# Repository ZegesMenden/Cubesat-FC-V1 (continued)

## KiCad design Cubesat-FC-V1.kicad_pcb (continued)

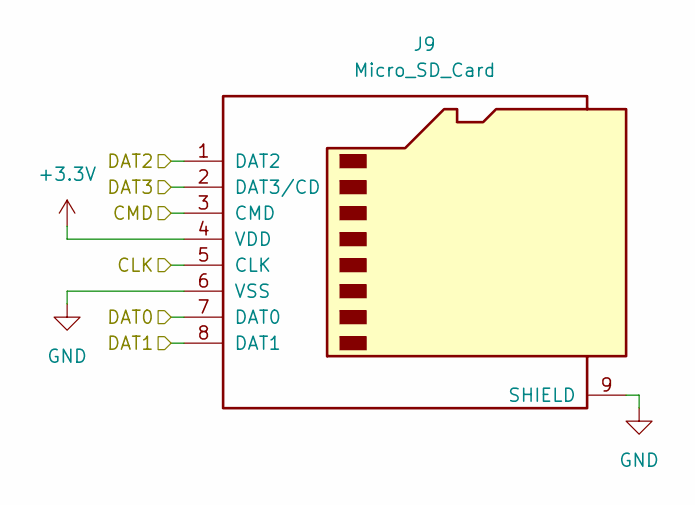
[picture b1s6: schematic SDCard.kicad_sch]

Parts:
J9: Micro_SD_Card; microSD_HC_Hirose_DM3D-SF

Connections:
+3.3V: J9.4 (VDD); also elsewhere on the board
/SD Card/CLK: J9.5 (CLK); also elsewhere on the board
/SD Card/CMD: J9.3 (CMD); also elsewhere on the board
/SD Card/DAT0: J9.7 (DAT0); also elsewhere on the board
/SD Card/DAT1: J9.8 (DAT1); also elsewhere on the board
/SD Card/DAT2: J9.1 (DAT2); also elsewhere on the board
/SD Card/DAT3: J9.2 (DAT3/CD); also elsewhere on the board
GND: J9.6 (VSS), J9.9 (SHIELD); also elsewhere on the board

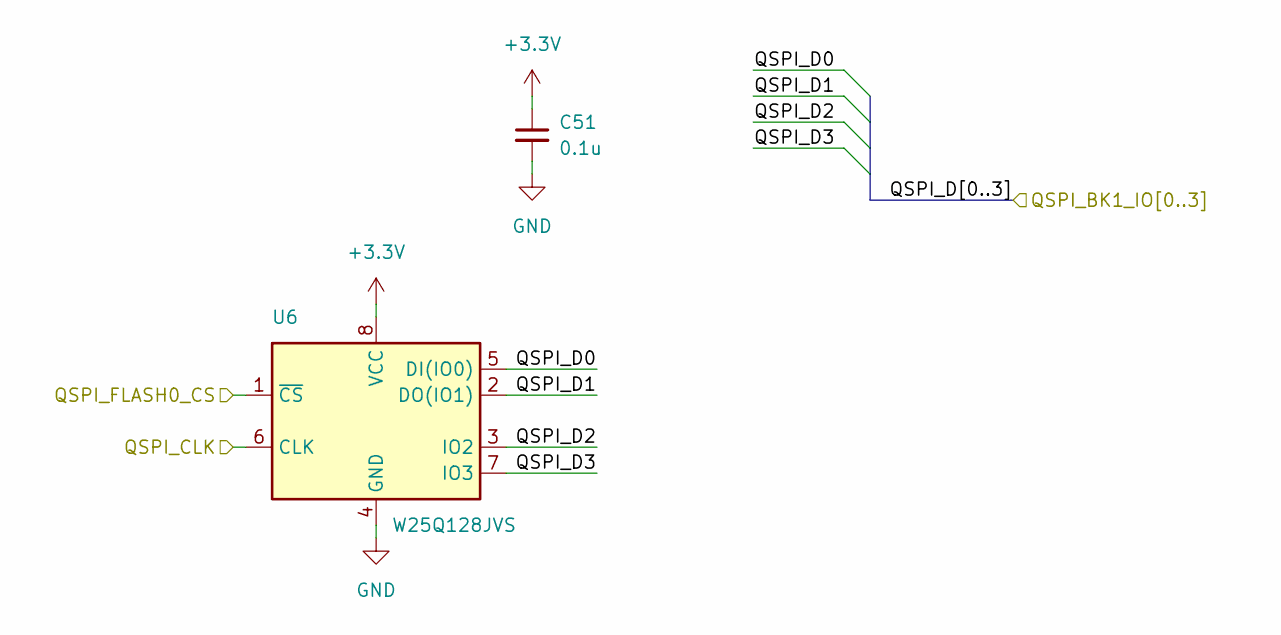
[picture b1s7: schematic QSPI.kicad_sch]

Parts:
C51: 0.1u; C_0402_1005Metric; voltage 10
U6: W25Q128JVS; SOIC-8_5.3x5.3mm_P1.27mm

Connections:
+3.3V: C51.1, U6.8 (VCC); also elsewhere on the board
/QSPI Flash/QSPI_D0: U6.5 (DI(IO0)); also elsewhere on the board
/QSPI Flash/QSPI_D1: U6.2 (DO(IO1)); also elsewhere on the board
/QSPI Flash/QSPI_D2: U6.3 (IO2); also elsewhere on the board
/QSPI Flash/QSPI_D3: U6.7 (IO3); also elsewhere on the board
/QSPI Flash/QSPI_FLASH0_CS: U6.1 (~CS); also elsewhere on the board
/STM32H747/QSPI_CLK: U6.6 (CLK); also elsewhere on the board
GND: C51.2, U6.4 (GND); also elsewhere on the board

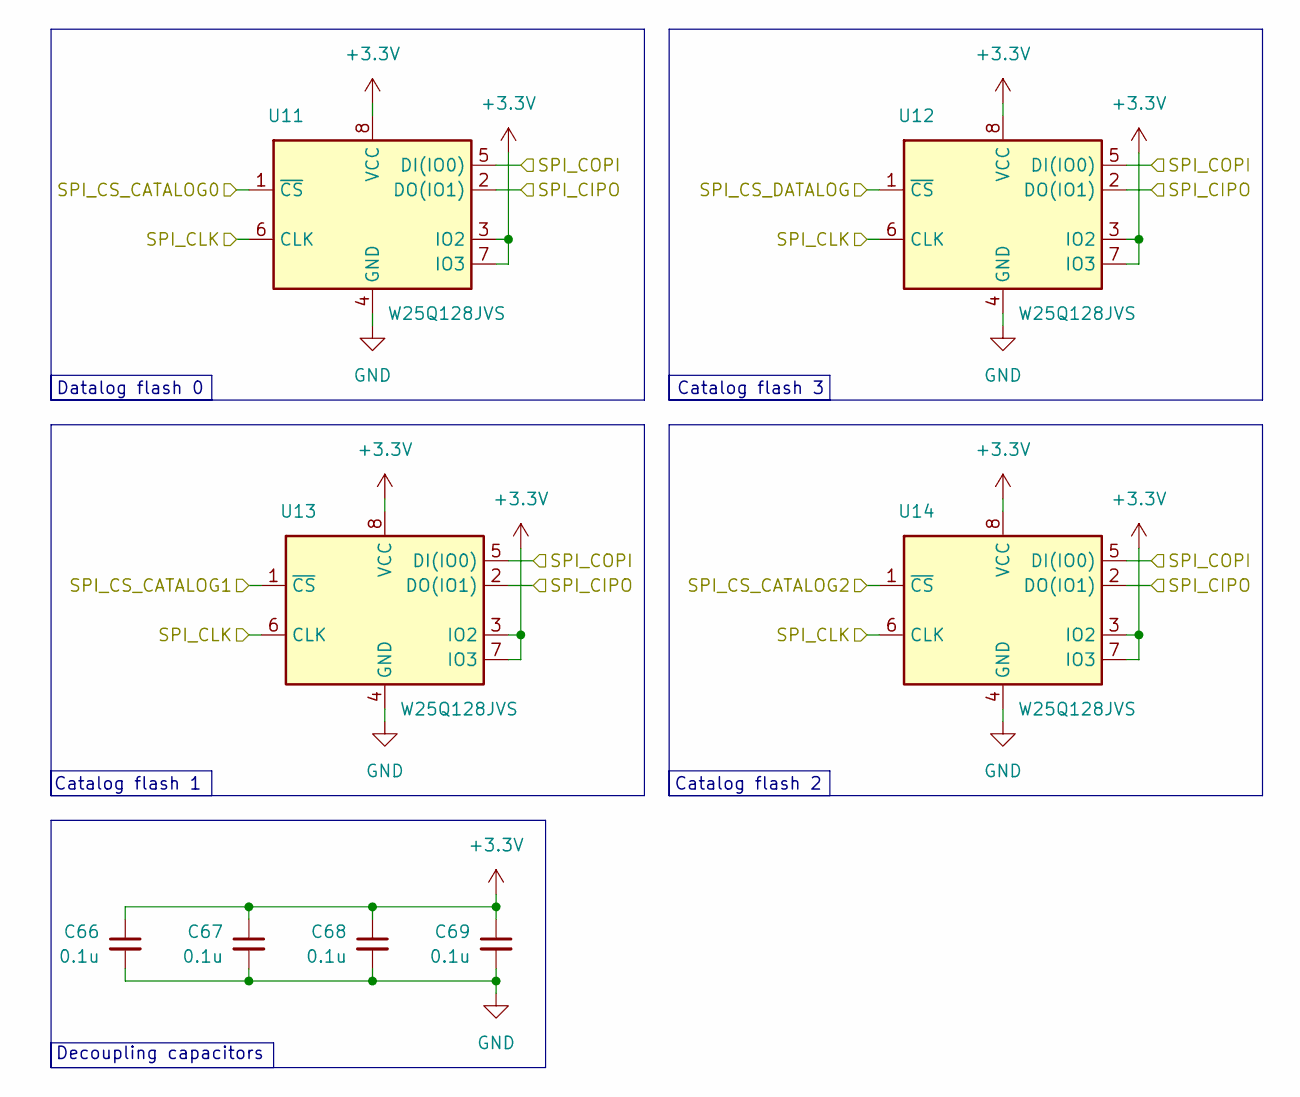
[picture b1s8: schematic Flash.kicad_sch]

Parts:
C66, C67, C68, C69: 0.1u; C_0402_1005Metric; voltage 10
U11, U12, U13, U14: W25Q128JVS; SOIC-8_5.3x5.3mm_P1.27mm

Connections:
+3.3V: C66.1, C67.1, C68.1, C69.1, U11.3 (IO2), U11.7 (IO3), U11.8 (VCC), U12.3 (IO2), U12.7 (IO3), U12.8 (VCC), U13.3 (IO2), U13.7 (IO3), U13.8 (VCC), U14.3 (IO2), U14.7 (IO3), U14.8 (VCC); also elsewhere on the board
/SPI1_CIPO: U11.2 (DO(IO1)), U12.2 (DO(IO1)), U13.2 (DO(IO1)), U14.2 (DO(IO1)); also elsewhere on the board
/SPI1_COPI: U11.5 (DI(IO0)), U12.5 (DI(IO0)), U13.5 (DI(IO0)), U14.5 (DI(IO0)); also elsewhere on the board
/SPI1_SCK: U11.6 (CLK), U12.6 (CLK), U13.6 (CLK), U14.6 (CLK); also elsewhere on the board
/SPI_CS_CATALOG0: U11.1 (~CS); also elsewhere on the board
/SPI_CS_CATALOG1: U13.1 (~CS); also elsewhere on the board
/SPI_CS_CATALOG2: U14.1 (~CS); also elsewhere on the board
/SPI_CS_DATALOG: U12.1 (~CS); also elsewhere on the board
GND: C66.2, C67.2, C68.2, C69.2, U11.4 (GND), U12.4 (GND), U13.4 (GND), U14.4 (GND); also elsewhere on the board

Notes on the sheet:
Decoupling capacitors
Catalog flash 1
Catalog flash 2
Datalog flash 0
Catalog flash 3

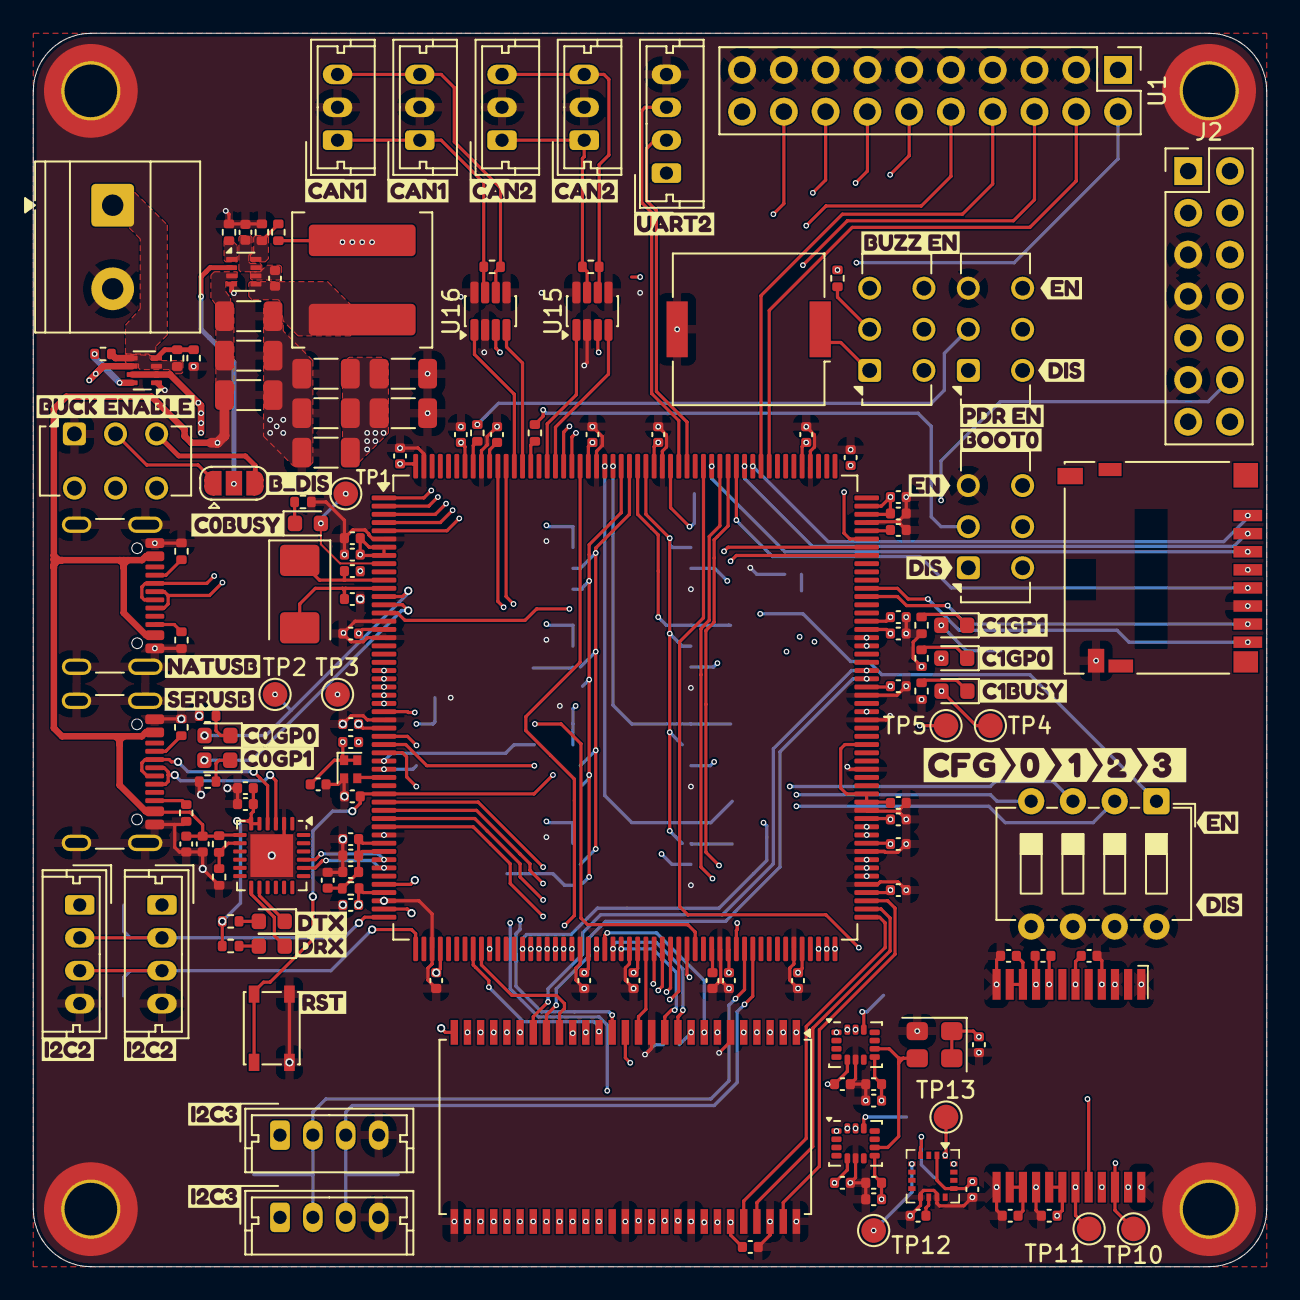
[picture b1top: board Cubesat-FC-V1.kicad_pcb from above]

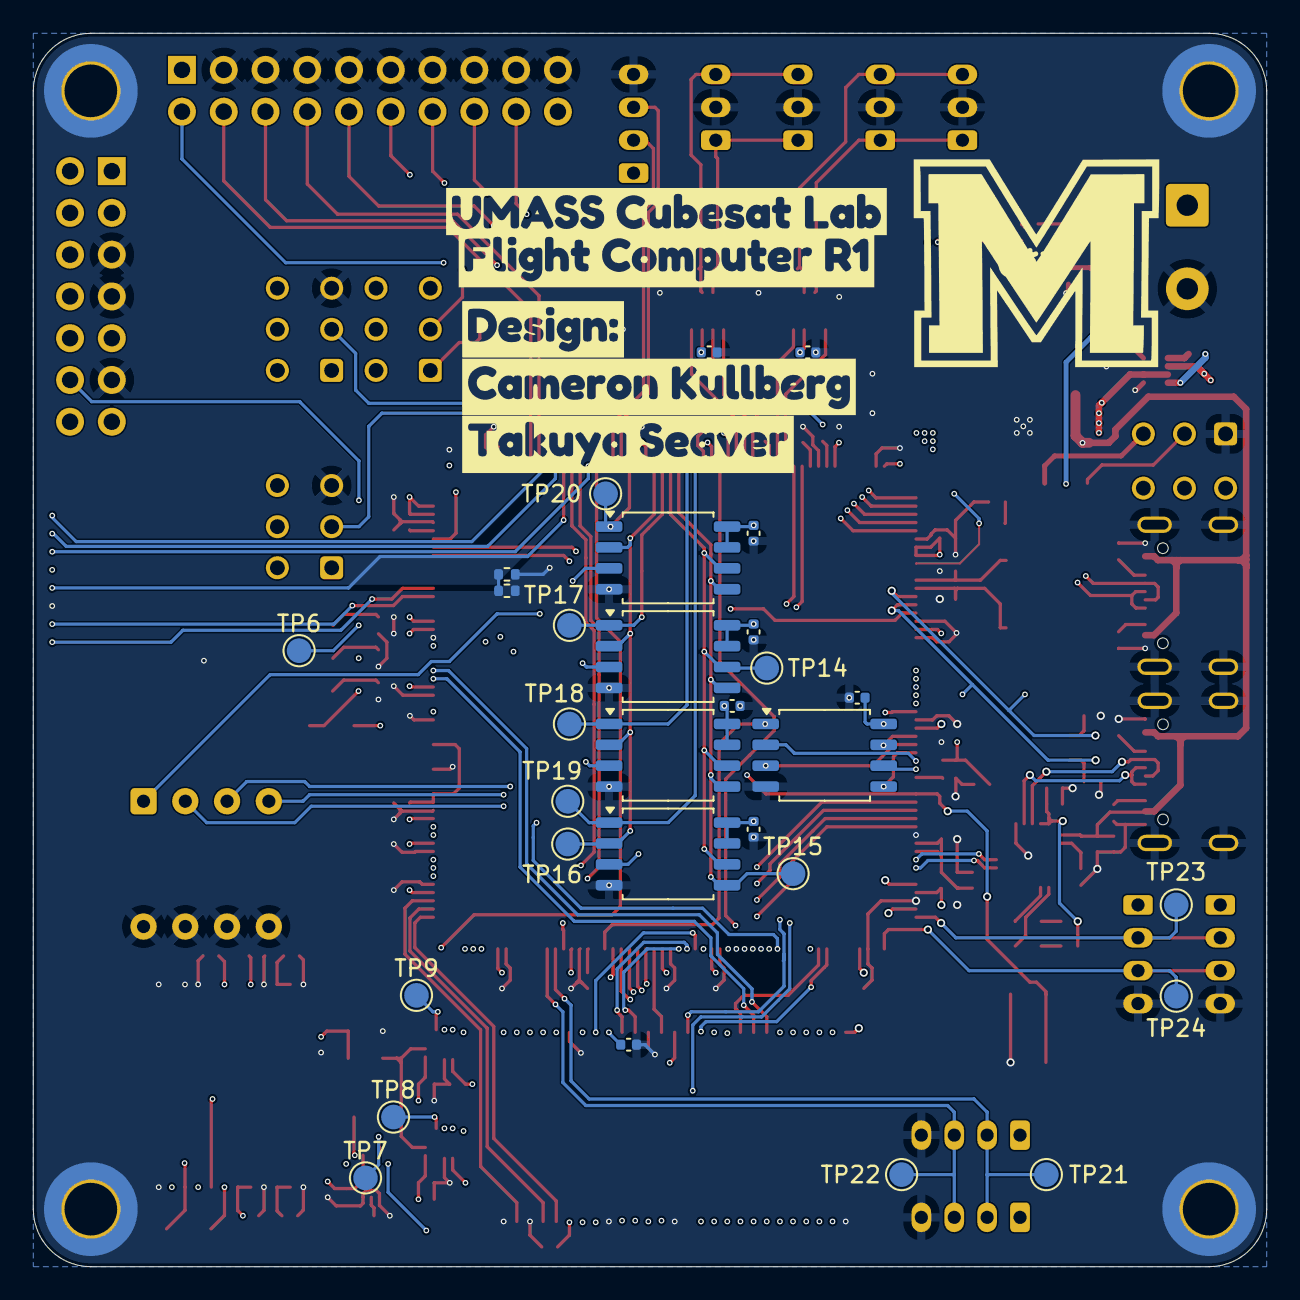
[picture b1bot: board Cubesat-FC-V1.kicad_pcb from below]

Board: 4 copper layers, 75.0 x 75.0 mm, 222 parts (35 on the bottom side), 157 nets.

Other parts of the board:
kibuzzard-69B9AFC9: G***; kibuzzard-69B9AFC9
kibuzzard-69B9BE8E: G***; kibuzzard-69B9BE8E
kibuzzard-69B9BE9C: G***; kibuzzard-69B9BE9C
kibuzzard-69B9BE81: G***; kibuzzard-69B9BE81
kibuzzard-69B64A9E: G***; kibuzzard-69B64A9E
kibuzzard-69B64AB5: G***; kibuzzard-69B64AB5
kibuzzard-69B64C2A, kibuzzard-69B64C2A#2: G***; kibuzzard-69B64C2A
kibuzzard-69B64C5E: G***; kibuzzard-69B64C5E
kibuzzard-69B64C7E, kibuzzard-69B64C7E#2: G***; kibuzzard-69B64C7E
kibuzzard-69B64C8D, kibuzzard-69B64C8D#2: G***; kibuzzard-69B64C8D
kibuzzard-69B64C48, kibuzzard-69B64C48#2: G***; kibuzzard-69B64C48
kibuzzard-69B64D23: G***; kibuzzard-69B64D23
kibuzzard-69B64D30: G***; kibuzzard-69B64D30
kibuzzard-69B64D62: G***; kibuzzard-69B64D62
kibuzzard-69B74E8C: G***; kibuzzard-69B74E8C
kibuzzard-69B753B2: G***; kibuzzard-69B753B2
kibuzzard-69B753C8: G***; kibuzzard-69B753C8
kibuzzard-69B755D8: G***; kibuzzard-69B755D8
kibuzzard-69B755DD: G***; kibuzzard-69B755DD
kibuzzard-69B7542C, kibuzzard-69B7542C#2: G***; kibuzzard-69B7542C
kibuzzard-69B7545E: G***; kibuzzard-69B7545E
kibuzzard-69B7546B: G***; kibuzzard-69B7546B
kibuzzard-69B75433, kibuzzard-69B75433#2: G***; kibuzzard-69B75433
kibuzzard-69B75457: G***; kibuzzard-69B75457
kibuzzard-69B75463: G***; kibuzzard-69B75463
kibuzzard-69B75470: G***; kibuzzard-69B75470
kibuzzard-69BF6ED0: G***; kibuzzard-69BF6ED0
kibuzzard-69BF6ED7: G***; kibuzzard-69BF6ED7
kibuzzard-69BF686D: G***; kibuzzard-69BF686D
kibuzzard-69BF735A: G***; kibuzzard-69BF735A
kibuzzard-69BF6875: G***; kibuzzard-69BF6875
kibuzzard-69BF7398: G***; kibuzzard-69BF7398
kibuzzard-69C071BD: G***; kibuzzard-69C071BD
kibuzzard-69C071CC: G***; kibuzzard-69C071CC
kibuzzard-69C071F5: G***; kibuzzard-69C071F5

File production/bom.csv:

Designator,Footprint,Quantity,Value,LCSC Part #
BZ1,Buzzer_Murata_PKMCS0909E,1,Buzzer,
"C1, C12, C13, C14, C15, C16, C17, C18, C19, C20, C21, C22, C23, C24, C25, C26, C27, C28, C29, C30, C31, C32, C33, C34, C35, C38, C46, C50, C51, C52, C54, C55, C58, C61, C66, C67, C68, C69, C75, C76",0402,40,0.1u,
C10,1206,1,100u,
"C2, C8, C9",1206,3,47u,
"C3, C7",1206,2,10u,
"C36, C37, C40, C45, C49, C56, C64",0402,7,1u,
C39,0402,1,4.7u,
"C4, C6",1206,2,0.1u,
"C41, C42, C43, C44, C57, C60",0402,6,2.2u,
"C47, C48",0402,2,??,
C5,0402,1,33n,
"C53, C63, C70, C71, C72, C73, C74, C77",0402,8,10u,
"C59, C62, C65",0402,3,10n,
"D1, D2, D3, D4, D5, D6, D7",0603,7,LED_G,
D8,0603,1,LED_R,
FB1,0402,1,???,
"J1, J12, J13, J3",Molex_Micro-Latch_53253-0370_1x03_P2.00mm_Vertical,4,Conn_01x03_Pin,
"J10, J4, J5, J6, J8",Molex_Micro-Latch_53253-0470_1x04_P2.00mm_Vertical,5,Conn_01x04_Pin,
"J11, J7",USB_C_Receptacle_GCT_USB4105-xx-A_16P_TopMnt_Horizontal,2,USB_C_Receptacle_USB2.0_14P,
J16,"TerminalBlock_Phoenix_MKDS-1,5-2-5.08_1x02_P5.08mm_Horizontal",1,Screw_Terminal_01x02,
J9,microSD_HC_Hirose_DM3D-SF,1,Micro_SD_Card,
L1,L_Coilcraft_XAL7070-XXX,1,5.6u,
"R1, R11, R2, R3, R4, R5, R6",0402,7,R_Small,
"R10, R9",0402,2,1k,
R12,0402,1,100,
R13,0402,1,30.9k,
R14,0402,1,10k,
R15,0402,1,68k,
"R18, R19",0402,2,120,
"R20, R22, R23",0402,3,20k,
R21,0402,1,47k,
"R24, R25, R7, R8",0402,4,5.1k,
"SW1, SW2",SW_CK_JS202011CQN_DPDT_Straight,2,SW_SPDT,
SW3,SW_DIP_SPSTx04_Slide_6.7x11.72mm_W7.62mm_P2.54mm_LowProfile,1,SW_DIP_x04,
SW4,SW_SPST_PTS810,1,SW_Button,
U1,PinSocket_2x10_P2.54mm_Vertical,1,~,
U10,SCH16T,1,~,
"U11, U12, U13, U14, U6",SOIC-8_5.3x5.3mm_P1.27mm,5,W25Q128JVS,
"U15, U16",SOIC-8_3.9x4.9mm_P1.27mm,2,MCP2558FD,
U18,QFN-24-1EP_4x4mm_P0.5mm_EP2.6x2.6mm,1,CP2102N-Axx-xQFN24,
U2,SOT-583-8,1,TPS2117DRL,
U3,SOT-583-8,1,TPS62933,
U4,LQFP-208_28x28mm_P0.5mm,1,STM32H757BITx,
U5,TSOP-II-54_22.2x10.16mm_P0.8mm,1,~,
"U7, U9",LGA-14_3x2.5mm_P0.5mm_LayoutBorder3x4y,2,~,
U8,LGA-16_3x3mm_P0.5mm,1,MMC5983MA,
Y1,Crystal_SMD_Abracon_ABM3-2Pin_5.0x3.2mm,1,32.768KHZ,
Y2,Oscillator_SMD_Abracon_ASCO-4Pin_1.6x1.2mm,1,ASCO,
Y3,Oscillator_SMD_Abracon_ASE-4Pin_3.2x2.5mm,1,ASE-xxxMHz,

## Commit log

2026-03-07 Finish IMS, finished more work on schematic
2026-03-09 Beginnings of routing
2026-03-16 more routing
2026-03-16 fix SDRAM routing
2026-03-22 Finish initial revision
2026-03-22 Formatting
2026-03-22 add R1 PDF
2026-03-25 Format filesystem
2026-04-09 R1 candidate
